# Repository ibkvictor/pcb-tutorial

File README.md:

# PCB Custom Component design
## CAD

## SCHEMATIC

## References
- [pcb design course](https://michaleruppe.com/learning/pcb-design-in-kicad-beginner-course/)

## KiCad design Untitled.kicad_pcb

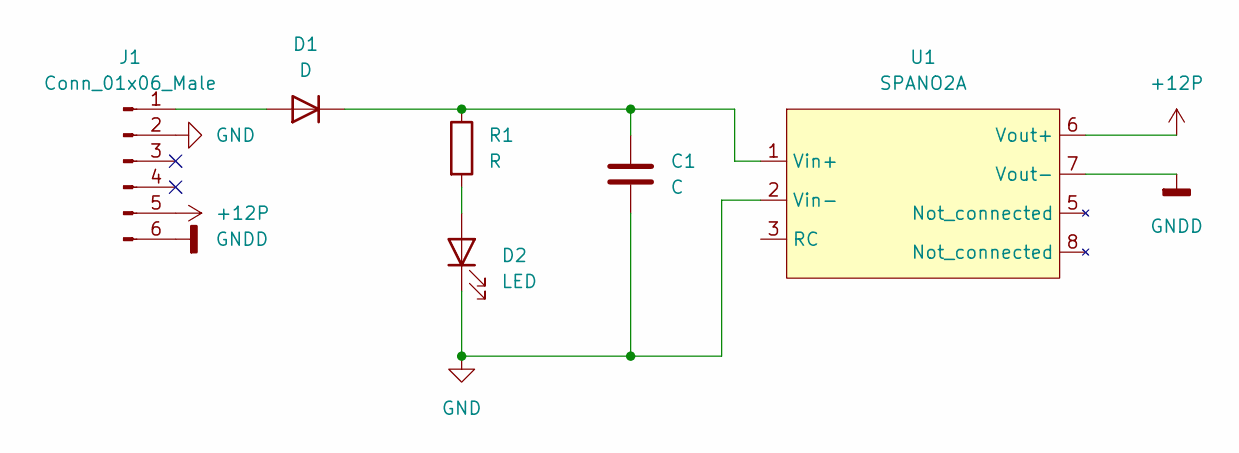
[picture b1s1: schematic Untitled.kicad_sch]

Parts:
C1: C; C_0805_2012Metric
D1: D; D_SMA
D2: LED; LED_0805_2012Metric
J1: Conn_01x06_Male; Molex_Micro-Fit_3.0_43045-0612_2x03_P3.00mm_Vertical
R1: R; R_0805_2012Metric
U1: SPANO2A; SPAN02

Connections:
+12P: J1.5, U1.6 (Vout+)
GND: C1.2, D2.1 (K), J1.2, U1.2 (Vin-)
GNDD: J1.6, U1.7 (Vout-)
unnamed: C1.1, D1.1 (K), R1.1, U1.1 (Vin+)
unnamed: D1.2 (A), J1.1
unnamed: D2.2 (A), R1.2

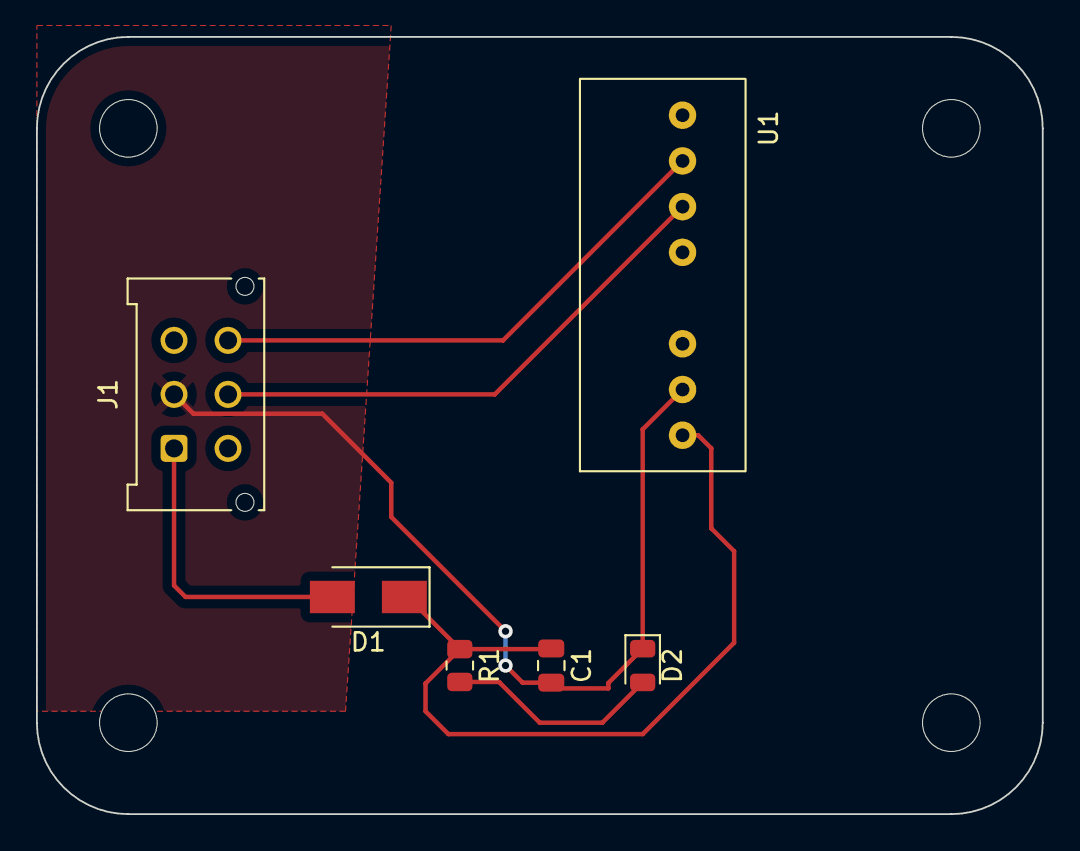
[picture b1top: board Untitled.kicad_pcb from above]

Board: 2 copper layers, 55.9 x 43.2 mm, 10 parts (0 on the bottom side), 6 nets.

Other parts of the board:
HOLE 1, HOLE 2, HOLE 3, HOLE 4: MountingHole_3.2mm_M3

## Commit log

2022-05-08 pcb files
2022-05-08 edited readme
